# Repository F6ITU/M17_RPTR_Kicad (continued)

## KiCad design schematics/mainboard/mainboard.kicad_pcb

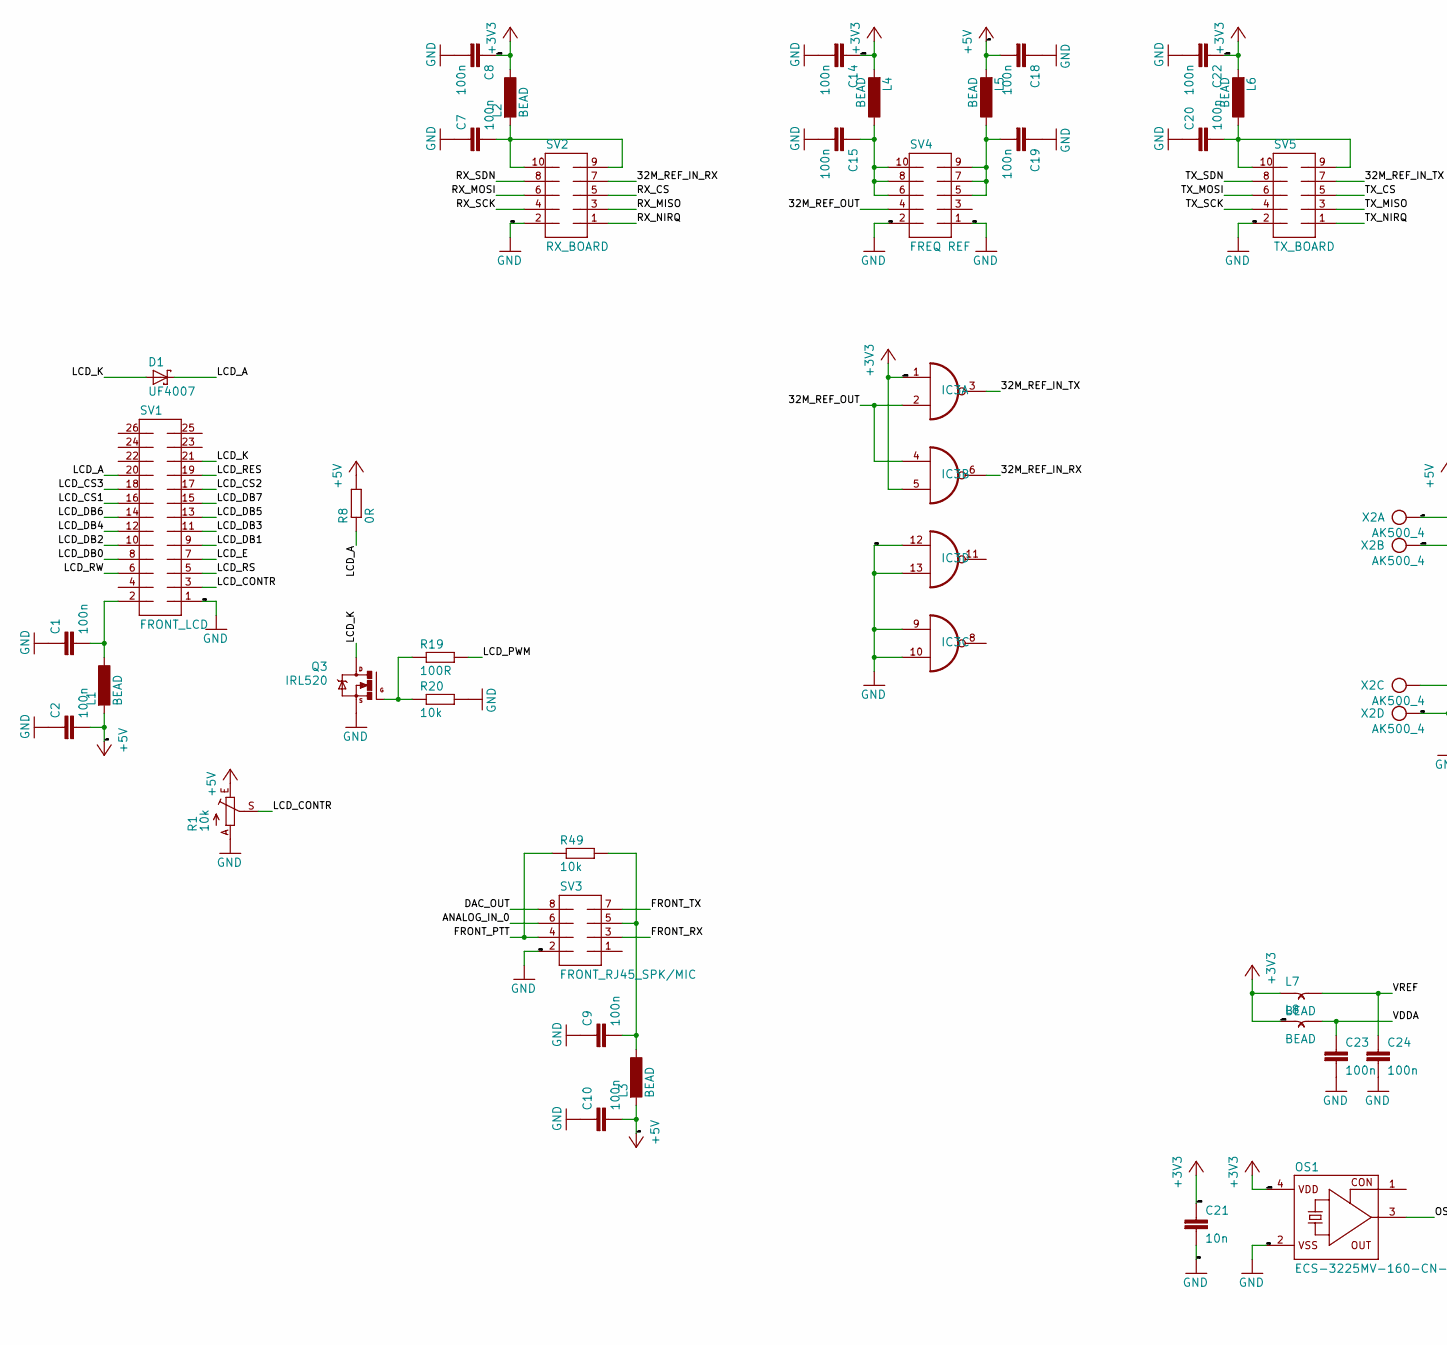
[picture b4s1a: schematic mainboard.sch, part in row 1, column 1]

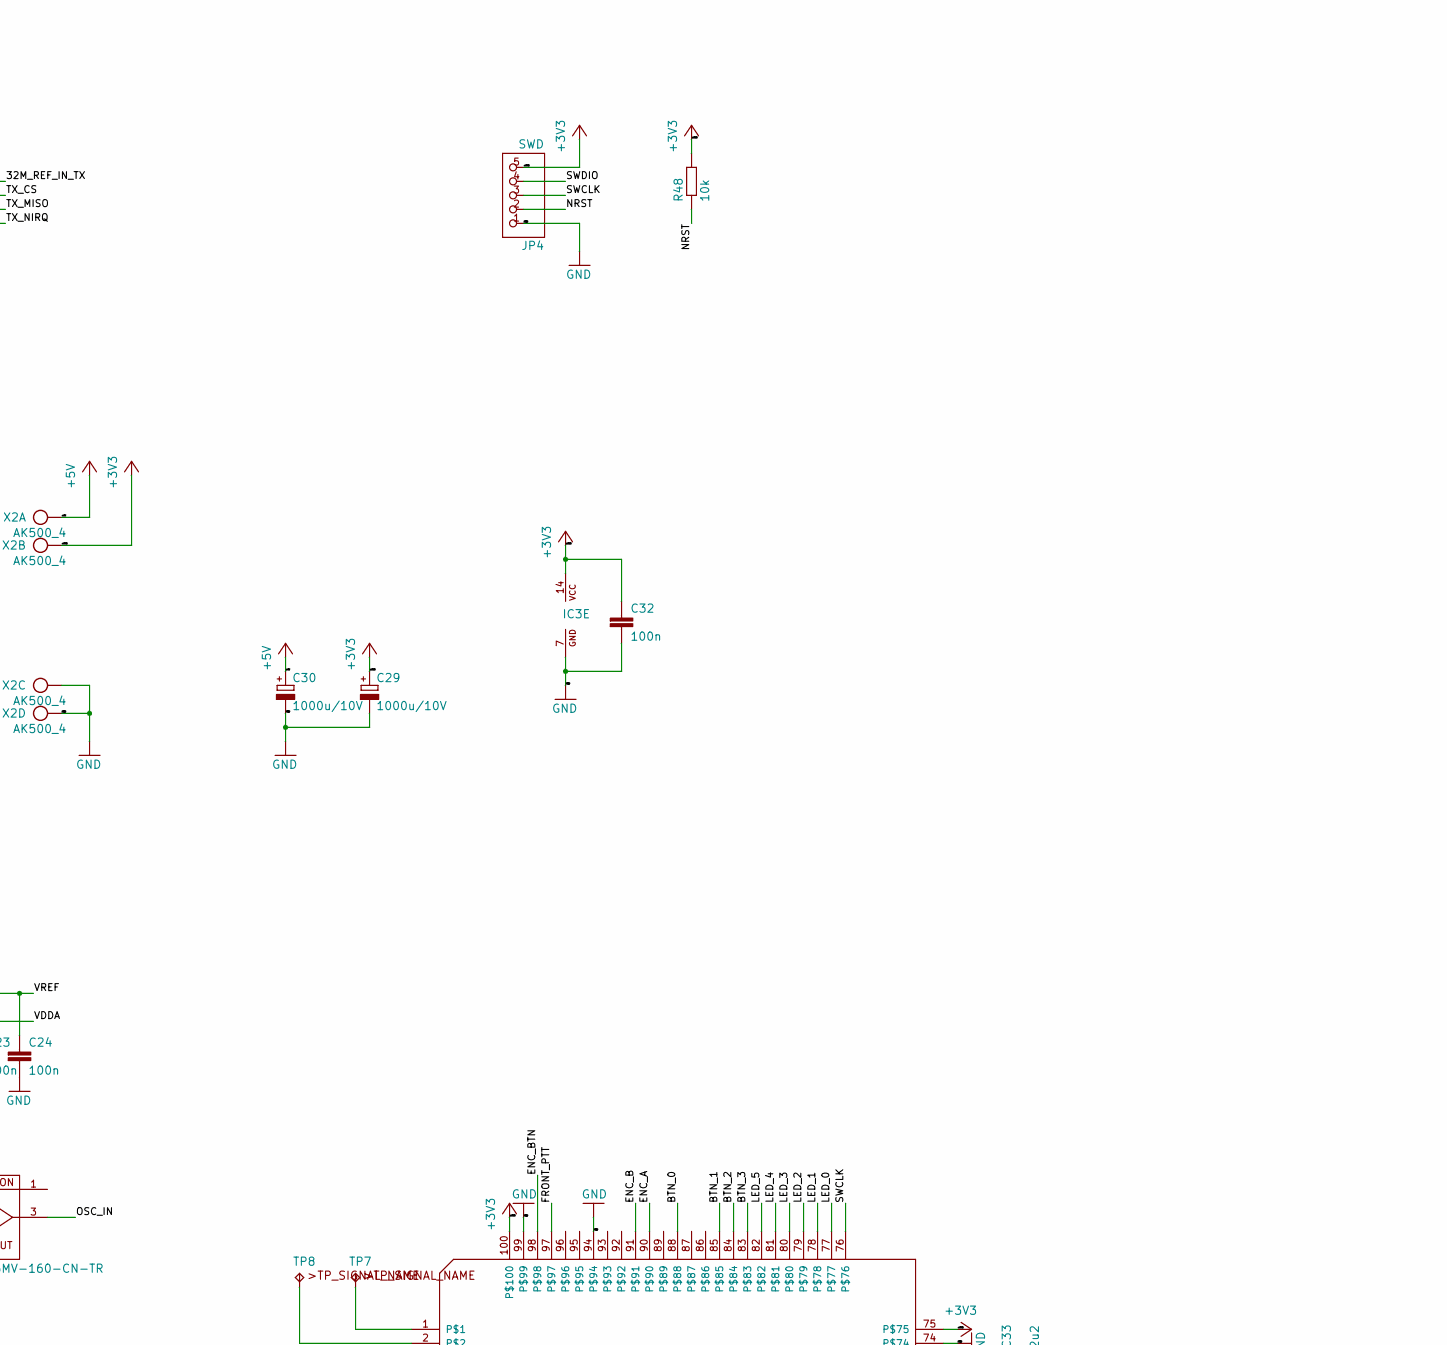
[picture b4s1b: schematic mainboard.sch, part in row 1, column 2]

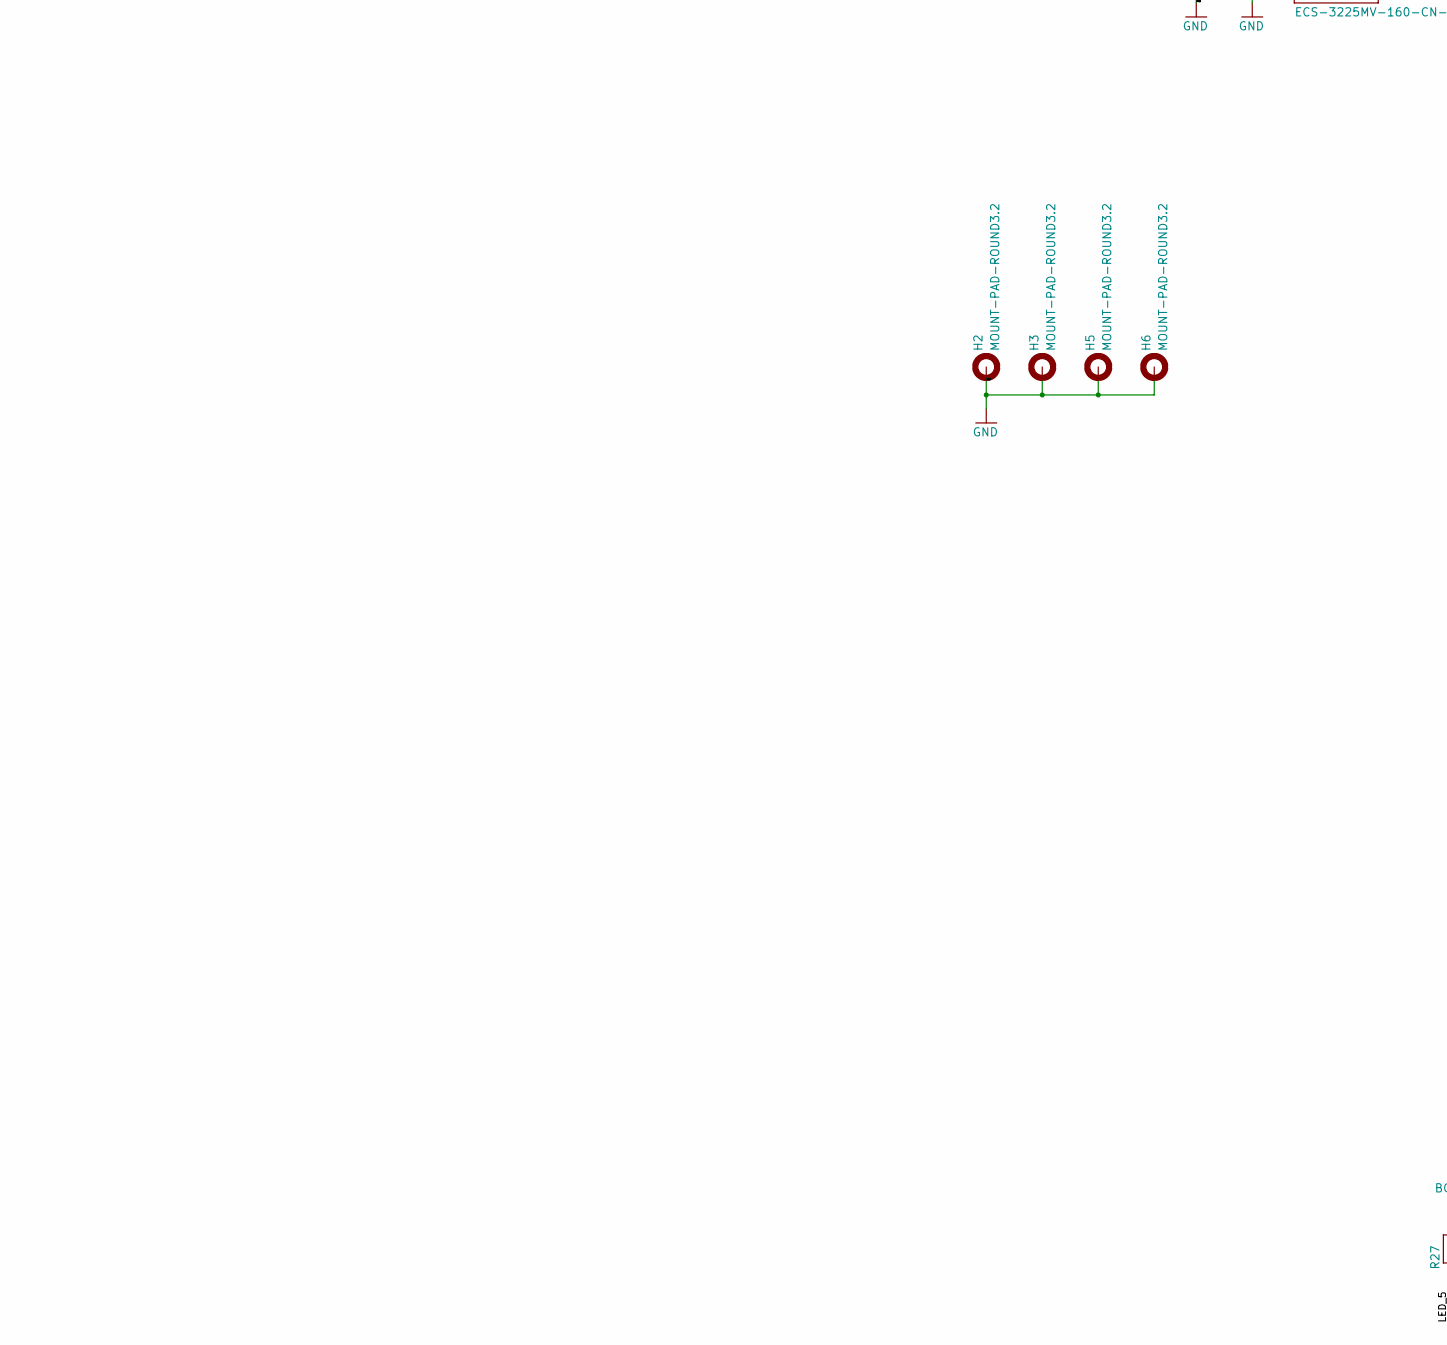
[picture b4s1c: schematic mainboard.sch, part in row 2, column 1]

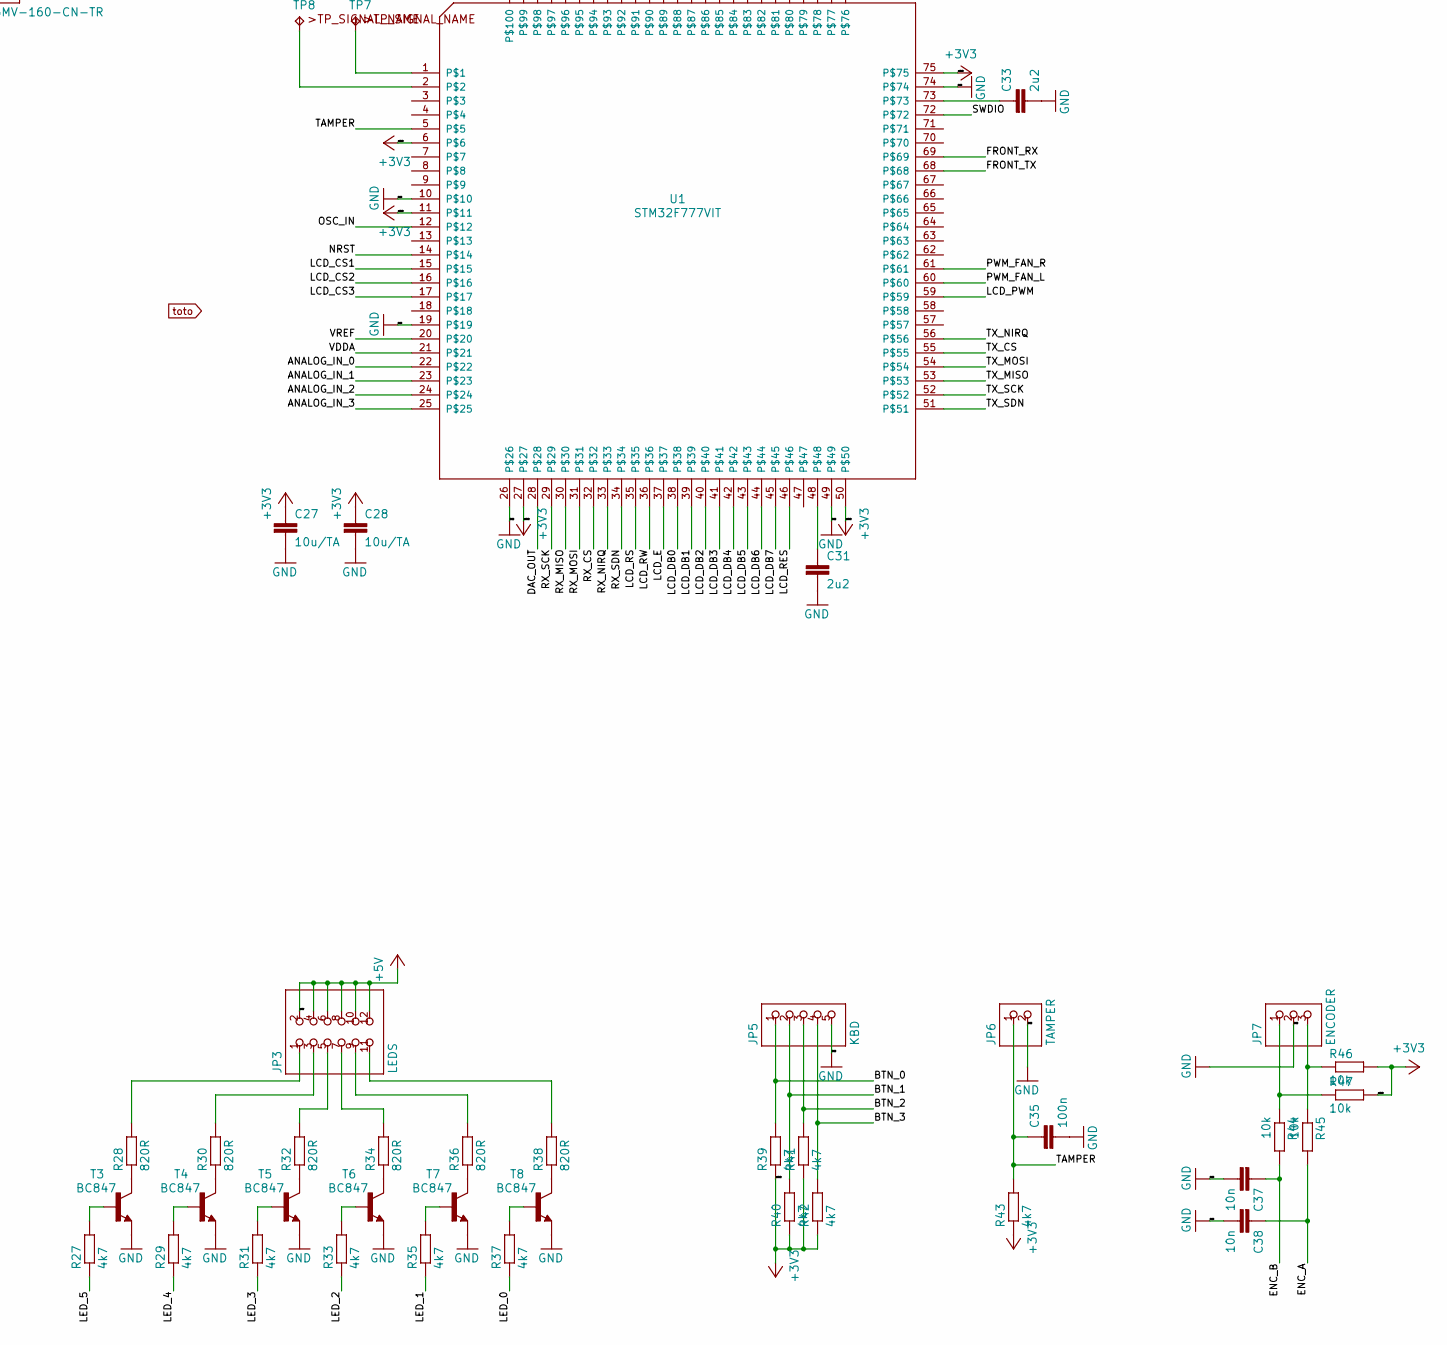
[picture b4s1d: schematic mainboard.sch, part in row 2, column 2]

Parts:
C1, C2, C7, C8, C9, C10, C14, C15, C18, C19, C20, C22, C23, C24, C32, C35: 100n; C0805
C21, C37, C38: 10n; C0805
C27, C28: 10u/TA; C1206
C29, C30: 1000u/10V; E3,5-8
C31, C33: 2u2; C0805
D1: UF4007; DO41-7.6
H2, H3, H5, H6: MOUNT-PAD-ROUND3.2; 3,2-PAD
IC3: 74AHC00D; SO14
JP3: LEDS; 2X06
JP4: SWD; 1X05
JP5: KBD; 1X05
JP6: TAMPER; 1X02
JP7: ENCODER; 1X03
L1, L2, L3, L4, L5, L6: BEAD; 0204_7
L7, L8: BEAD; SM-B5
OS1: ECS-3225MV-160-CN-TR; 3.4X2.7-4-PAD
Q3: IRL520; TO220BV
R1: 10k; CA6V
R8: 0R; R1206
R19: 100R; R0805
R20, R44, R45, R46, R47, R48, R49: 10k; R0805
R27, R29, R31, R33, R35, R37, R39, R40, R41, R42, R43: 4k7; R0805
R28, R30, R32, R34, R36, R38: 820R; R0805
SV1: FRONT_LCD; ML26
SV2: RX_BOARD; ML10
SV3: FRONT_RJ45_SPK/MIC; MA04-2
SV4: FREQ REF; ML10
SV5: TX_BOARD; ML10
T3, T4, T5, T6, T7, T8: BC847; SOT23
TP7, TP8: TPB2,54; B2,54
U1: STM32F777VIT; LQFP100
X2: AK500_4

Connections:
+3V3: C8.1, C14.1, C21.1, C22.1, C27.1, C28.1, C29.+, C32.1, IC3.1 (I0), IC3.5 (I1), IC3.14 (VCC), JP4.5, L2.1, L4.2, L6.2, L7.1, L8.1, OS1.4 (VDD), R39.1, R40.1, R41.1, R42.1, R43.1, R46.2, R47.2, R48.2, U1.6, U1.11, U1.27, U1.50, U1.75, U1.100, X2.2
+5V: C2.2, C10.2, C18.2, C30.+, JP3.2, JP3.4, JP3.6, JP3.8, JP3.10, JP3.12, L1.2, L3.2, L5.2, R1.E, R8.2, X2.1
/32M_REF_IN_RX: IC3.6 (O), SV2.7
/32M_REF_IN_TX: IC3.3 (O), SV5.7
/32M_REF_OUT: IC3.2 (I1), IC3.4 (I0), SV4.4
/ANALOG_IN_0: SV3.6, U1.22
/ANALOG_IN_1: U1.23
/ANALOG_IN_2: U1.24
/ANALOG_IN_3: U1.25
/BTN_0: JP5.1, R39.2, U1.88
/BTN_1: JP5.2, R40.2, U1.85
/BTN_2: JP5.3, R41.2, U1.84
/BTN_3: JP5.4, R42.2, U1.83
/DAC_OUT: SV3.8, U1.28
/ENC_A: C38.1, R45.2, U1.90
/ENC_B: C37.1, R44.2, U1.91
/ENC_BTN: U1.98
/FRONT_PTT: R49.1, SV3.4, U1.97
/FRONT_RX: SV3.3, U1.69
/FRONT_TX: SV3.7, U1.68
/LCD_A: D1.C, R8.1, SV1.20
/LCD_CONTR: R1.S, SV1.3
/LCD_CS1: SV1.16, U1.15
/LCD_CS2: SV1.17, U1.16
/LCD_CS3: SV1.18, U1.17
/LCD_DB0: SV1.8, U1.38
/LCD_DB1: SV1.9, U1.39
/LCD_DB2: SV1.10, U1.40
/LCD_DB3: SV1.11, U1.41
/LCD_DB4: SV1.12, U1.42
/LCD_DB5: SV1.13, U1.43
/LCD_DB6: SV1.14, U1.44
/LCD_DB7: SV1.15, U1.45
/LCD_E: SV1.7, U1.37
/LCD_K: D1.A, Q3.D, SV1.21
/LCD_PWM: R19.2, U1.59
/LCD_RES: SV1.19, U1.46
/LCD_RS: SV1.5, U1.35
/LCD_RW: SV1.6, U1.36
/LED_0: R37.1, U1.77
/LED_1: R35.1, U1.78
/LED_2: R33.1, U1.79
/LED_3: R31.1, U1.80
/LED_4: R29.1, U1.81
/LED_5: R27.1, U1.82
/NRST: JP4.2, R48.1, U1.14
/OSC_IN: OS1.3 (OUT), U1.12
/PWM_FAN_L: U1.60
/PWM_FAN_R: U1.61
/RX_CS: SV2.5, U1.32
/RX_MISO: SV2.3, U1.30
/RX_MOSI: SV2.6, U1.31
/RX_NIRQ: SV2.1, U1.33
/RX_SCK: SV2.4, U1.29
/RX_SDN: SV2.8, U1.34
/SWCLK: JP4.3, U1.76
/SWDIO: JP4.4, U1.72
/TAMPER: C35.1, JP6.1, R43.2, U1.5
/TX_CS: SV5.5, U1.55
/TX_MISO: SV5.3, U1.53
/TX_MOSI: SV5.6, U1.54
/TX_NIRQ: SV5.1, U1.56
/TX_SCK: SV5.4, U1.52
/TX_SDN: SV5.8, U1.51
/VDDA: C23.1, L8.2, U1.21
/VREF: C24.1, L7.2, U1.20
GND: C1.1, C2.1, C7.1, C8.2, C9.1, C10.1, C14.2, C15.2, C18.1, C19.1, C20.1, C21.2, C22.2, C23.2, C24.2, C27.2, C28.2, C29.-, C30.-, C31.2, C32.2, C33.2, C35.2, C37.2, C38.2, H2.B3,2, H3.B3,2, H5.B3,2, H6.B3,2, IC3.7 (GND), IC3.9 (I0), IC3.10 (I1), IC3.12 (I0), IC3.13 (I1), JP4.1, JP5.5, JP6.2, JP7.2, OS1.2 (VSS), Q3.S, R1.A, R20.2, SV1.1, SV2.2, SV3.2, SV4.1, SV4.2, SV5.2, T3.2 (E), T4.2 (E), T5.2 (E), T6.2 (E), T7.2 (E), T8.2 (E), U1.10, U1.19, U1.26, U1.49, U1.74, U1.94, U1.99, X2.3, X2.4
unnamed: C1.2, L1.1, SV1.2
unnamed: C7.2, L2.2, SV2.9, SV2.10
unnamed: C9.2, L3.1, R49.2, SV3.5
unnamed: C15.1, L4.1, SV4.6, SV4.8, SV4.10
unnamed: C19.2, L5.1, SV4.5, SV4.7, SV4.9
unnamed: C20.2, L6.1, SV5.9, SV5.10
unnamed: C31.1, U1.48
unnamed: C33.1, U1.73
unnamed: JP3.1, R28.2
unnamed: JP3.3, R30.2
unnamed: JP3.5, R32.2
unnamed: JP3.7, R34.2
unnamed: JP3.9, R36.2
unnamed: JP3.11, R38.2
unnamed: JP7.1, R44.1, R47.1
unnamed: JP7.3, R45.1, R46.1
unnamed: Q3.G, R19.1, R20.1
unnamed: R27.2, T3.1 (B)
unnamed: R28.1, T3.3 (C)
unnamed: R29.2, T4.1 (B)
unnamed: R30.1, T4.3 (C)
unnamed: R31.2, T5.1 (B)
unnamed: R32.1, T5.3 (C)
unnamed: R33.2, T6.1 (B)
unnamed: R34.1, T6.3 (C)
unnamed: R35.2, T7.1 (B)
unnamed: R36.1, T7.3 (C)
unnamed: R37.2, T8.1 (B)
unnamed: R38.1, T8.3 (C)
unnamed: TP7.TP, U1.1
unnamed: TP8.TP, U1.2

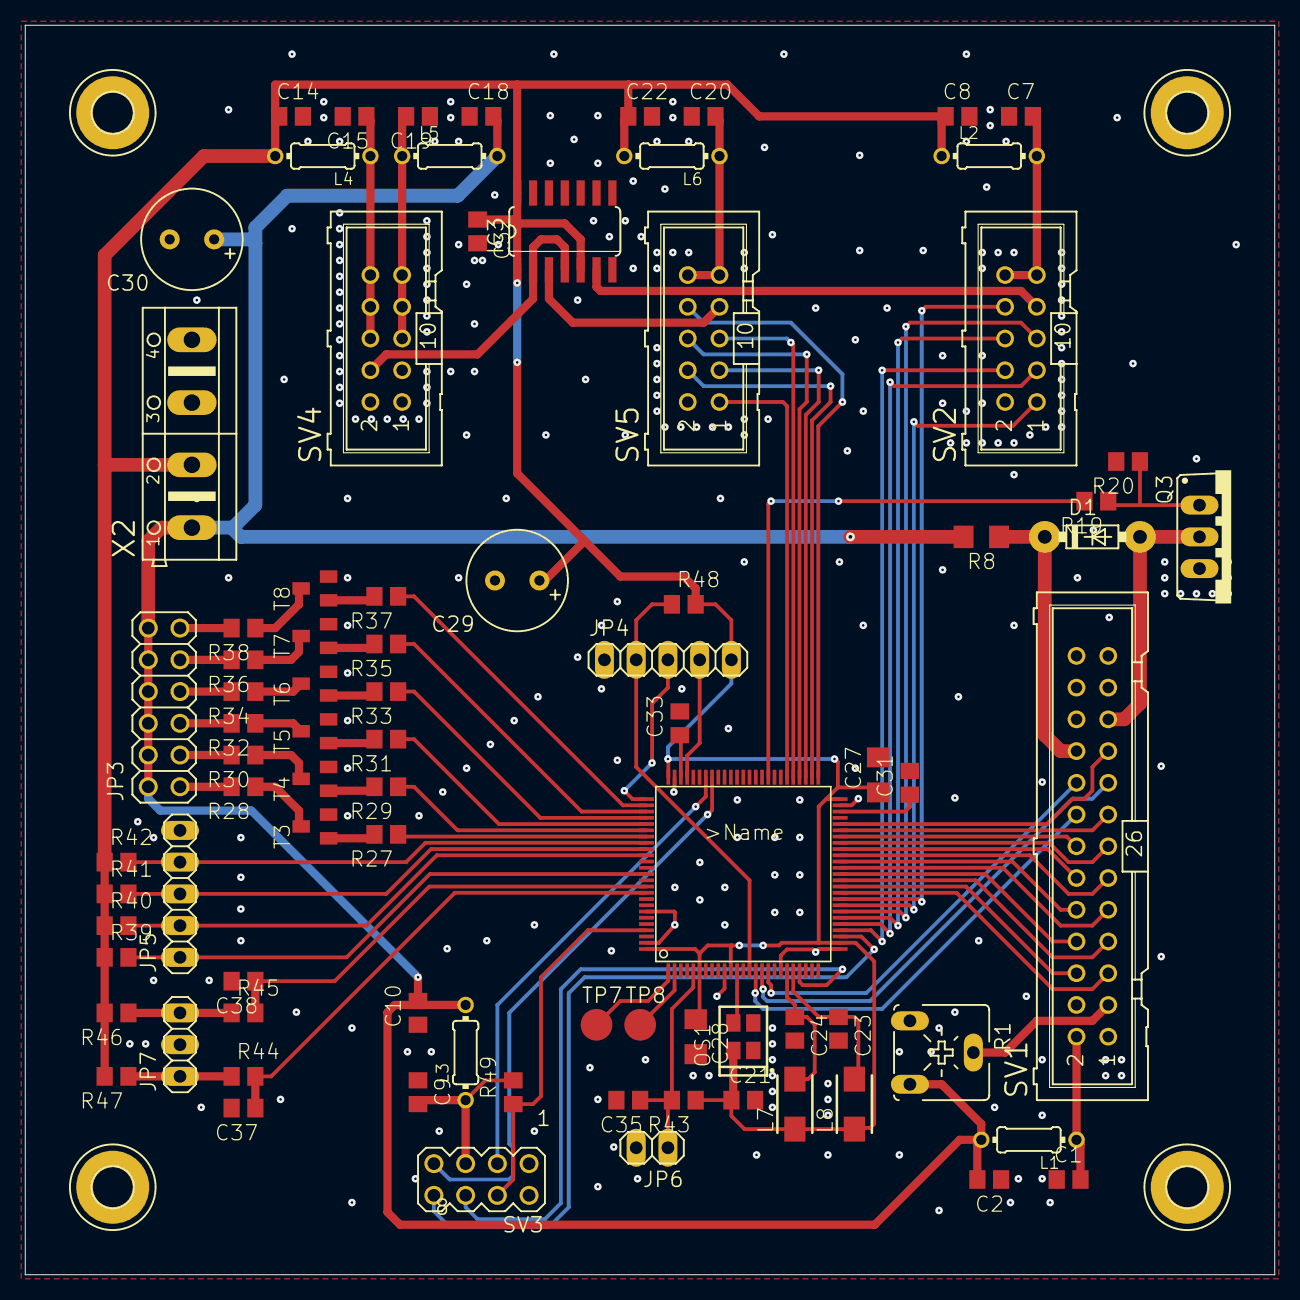
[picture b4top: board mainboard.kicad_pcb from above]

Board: 2 copper layers, 100.0 x 100.0 mm, 88 parts (0 on the bottom side), 92 nets.

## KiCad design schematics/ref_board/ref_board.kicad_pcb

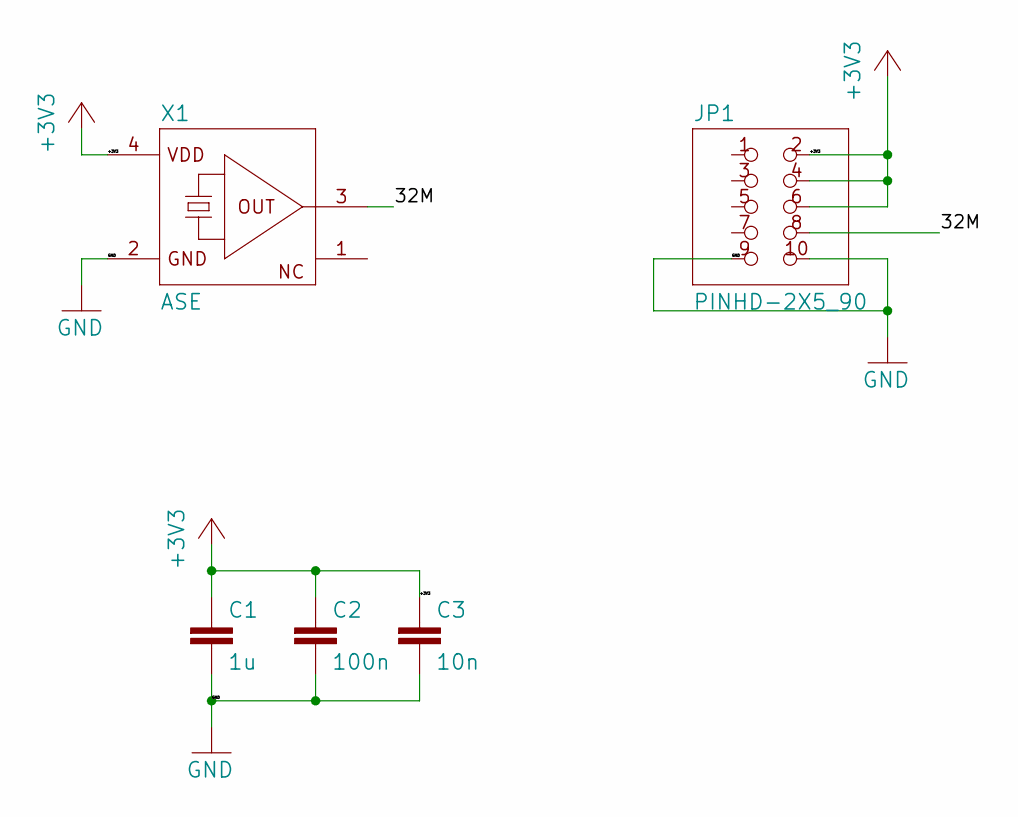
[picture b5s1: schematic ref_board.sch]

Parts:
C1: 1u; C1206
C2: 100n; C0805
C3: 10n; C0805
JP1: PINHD-2X5_90; 2X05_90
X1: ASE

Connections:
+3V3: C1.1, C2.1, C3.1, JP1.2, JP1.4, JP1.6, X1.4 (VDD)
/32M: JP1.8, X1.3 (OUT)
GND: C1.2, C2.2, C3.2, JP1.9, JP1.10, X1.2 (GND)

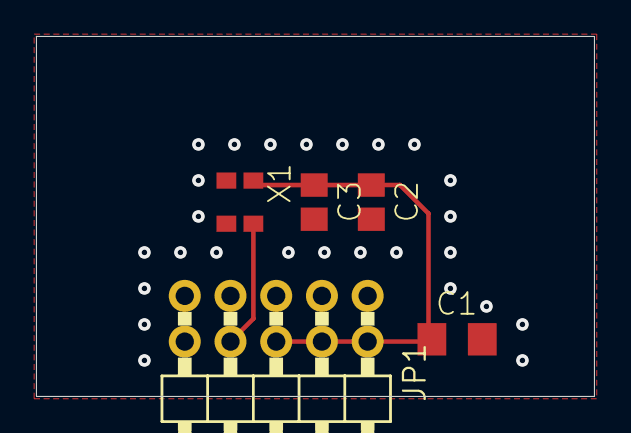
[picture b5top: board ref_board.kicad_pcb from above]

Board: 2 copper layers, 31.0 x 20.0 mm, 5 parts (0 on the bottom side), 3 nets.

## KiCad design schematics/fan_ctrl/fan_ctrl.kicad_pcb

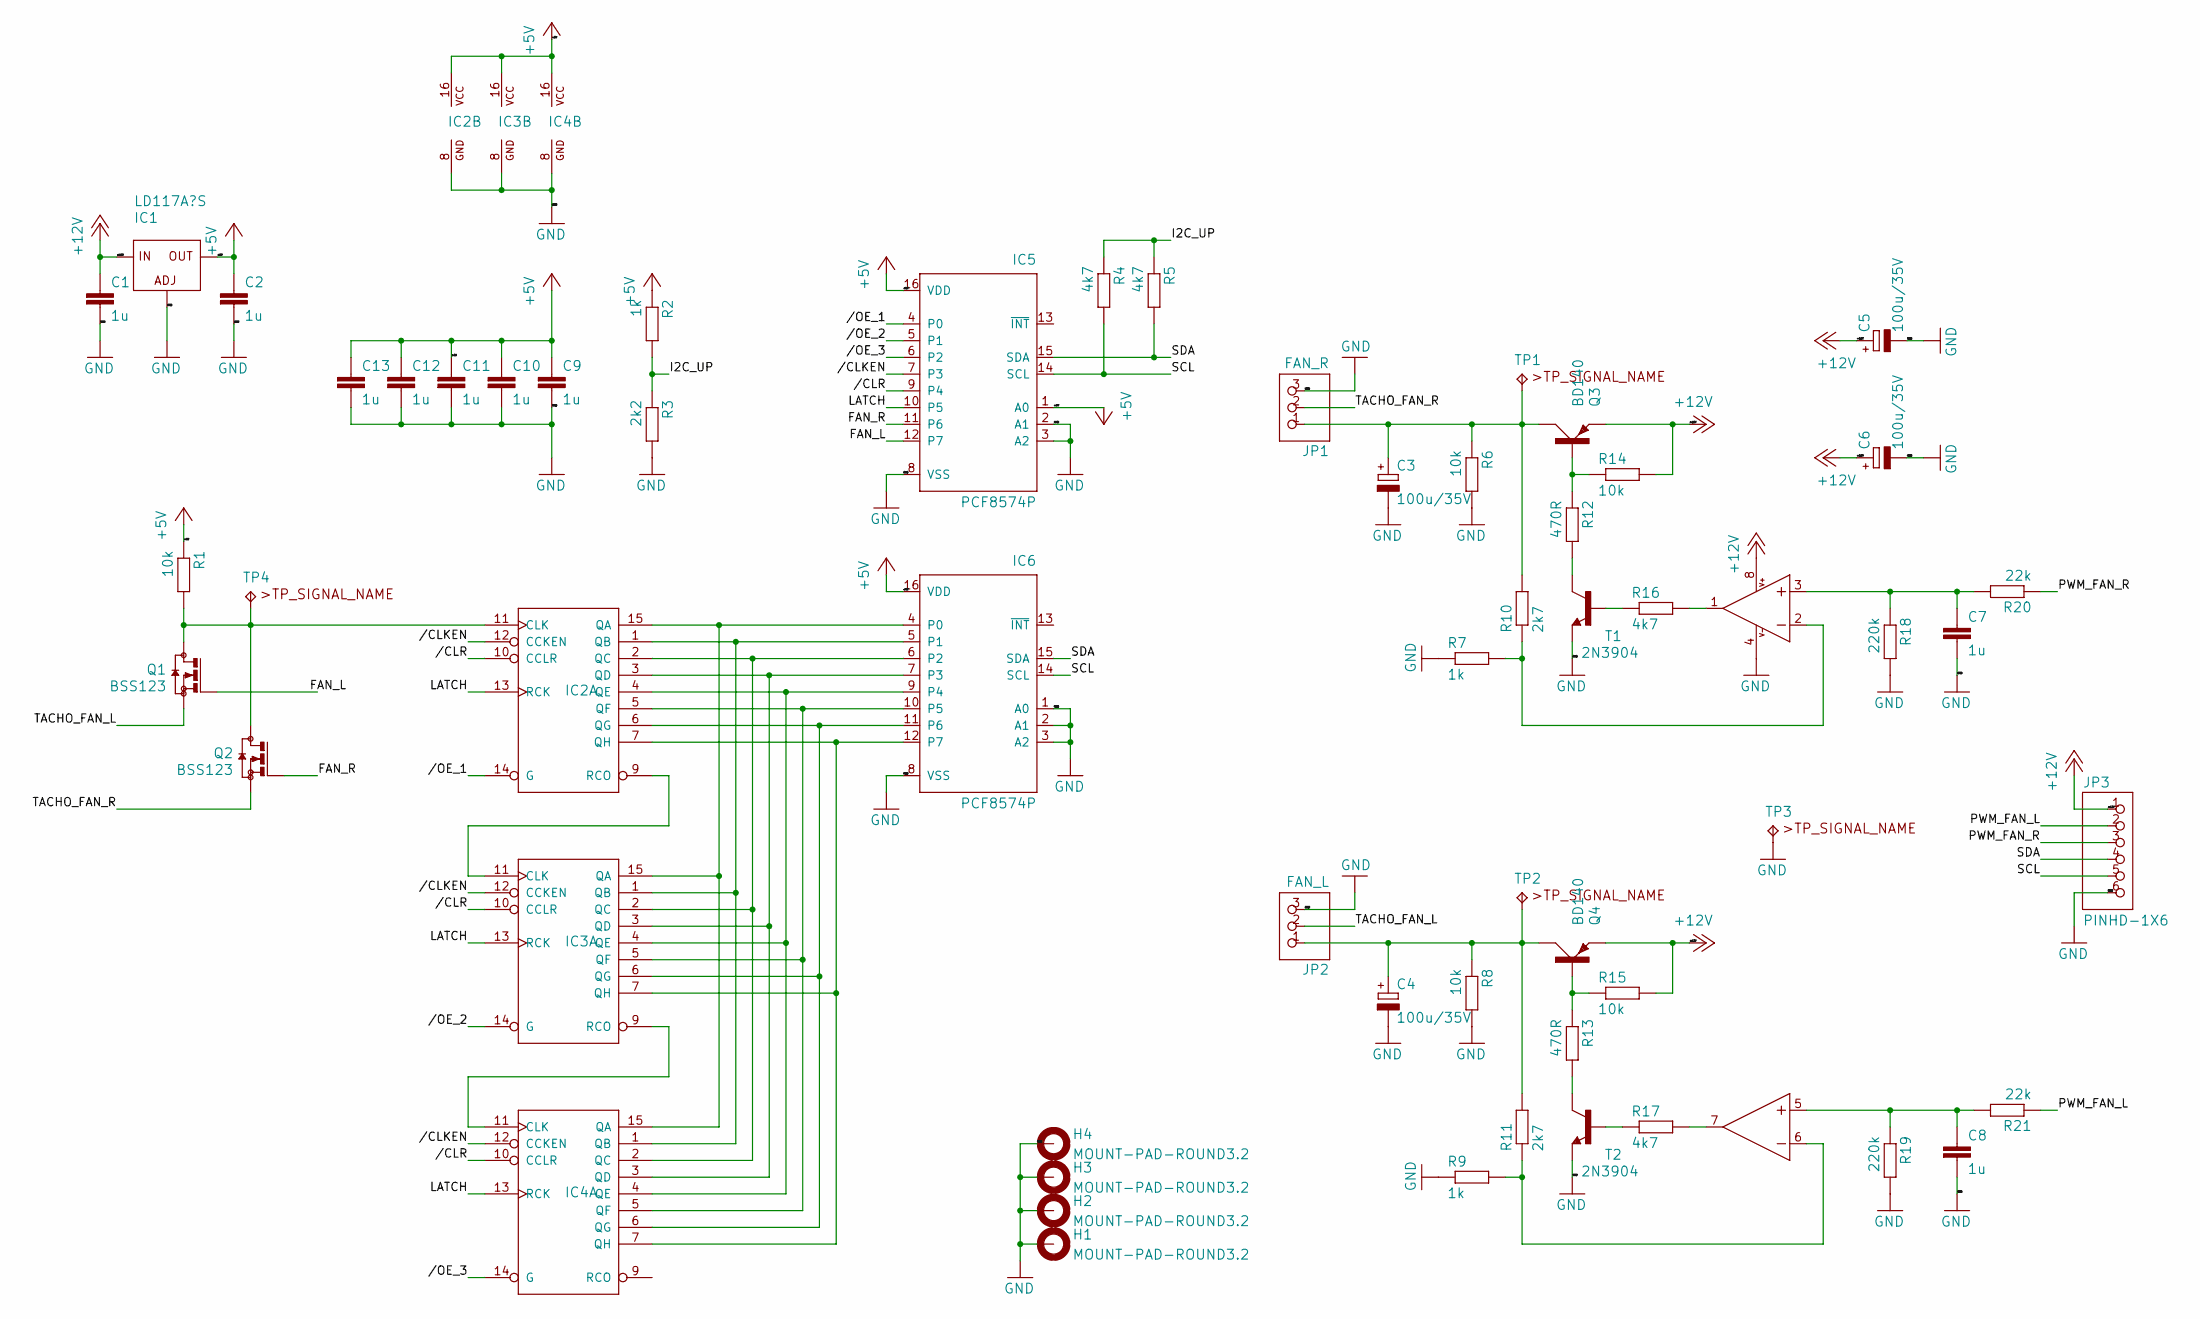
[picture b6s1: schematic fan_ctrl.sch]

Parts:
C1, C2, C7, C8, C9, C10, C11, C12, C13: 1u; C0805
C3, C4, C5, C6: 100u/35V; E3,5-8
H1, H2, H3, H4: MOUNT-PAD-ROUND3.2; 3,2-PAD
IC1: LD117A?S; SOT223
IC2, IC3, IC4: 74590N; DIL16
IC5, IC6: PCF8574P; DIL16
IC7: LM358N; DIL08
JP1: FAN_R; 1X03
JP2: FAN_L; 1X03
JP3: PINHD-1X6; 1X06
Q1, Q2: BSS123; SOT23
Q3, Q4: BD140; TO126AV
R1, R6, R8, R14, R15: 10k; R0805
R2, R7, R9: 1k; R0805
R3: 2k2; R0805
R4, R5, R16, R17: 4k7; R0805
R10, R11: 2k7; R0805
R12, R13: 470R; R0805
R18, R19: 220k; R0805
R20, R21: 22k; R0805
T1, T2: 2N3904; TO92-EBC
TP1, TP2, TP3, TP4: TPB2,54; B2,54

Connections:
+5V: C2.1, C9.1, C10.1, C11.1, C12.1, C13.1, IC1.4 (OUT), IC2.16 (VCC), IC3.16 (VCC), IC4.16 (VCC), IC5.1 (A0), IC5.16 (VDD), IC6.16 (VDD), R1.1, R2.1
+12V: C1.1, C5.+, C6.+, IC1.3 (IN), IC7.8 (V+), JP3.1, Q3.E, Q4.E, R14.2, R15.2
//CLKEN: IC2.12 (CCKEN), IC3.12 (CCKEN), IC4.12 (CCKEN), IC5.7 (P3)
//CLR: IC2.10 (CCLR), IC3.10 (CCLR), IC4.10 (CCLR), IC5.9 (P4)
//OE_1: IC2.14 (G), IC5.4 (P0)
//OE_2: IC3.14 (G), IC5.5 (P1)
//OE_3: IC4.14 (G), IC5.6 (P2)
/FAN_L: IC5.12 (P7), Q1.1 (G)
/FAN_R: IC5.11 (P6), Q2.1 (G)
/I2C_UP: R2.2, R3.1, R4.1, R5.1
/LATCH: IC2.13 (RCK), IC3.13 (RCK), IC4.13 (RCK), IC5.10 (P5)
/PWM_FAN_L: JP3.2, R21.1
/PWM_FAN_R: JP3.3, R20.1
/SCL: IC5.14 (SCL), IC6.14 (SCL), JP3.5, R4.2
/SDA: IC5.15 (SDA), IC6.15 (SDA), JP3.4, R5.2
/TACHO_FAN_L: JP2.2, Q1.2 (S)
/TACHO_FAN_R: JP1.2, Q2.2 (S)
GND: C1.2, C2.2, C3.-, C4.-, C5.-, C6.-, C7.2, C8.2, C9.2, C10.2, C11.2, C12.2, C13.2, H1.B3,2, H2.B3,2, H3.B3,2, H4.B3,2, IC1.1 (ADJ), IC2.8 (GND), IC3.8 (GND), IC4.8 (GND), IC5.2 (A1), IC5.3 (A2), IC5.8 (VSS), IC6.1 (A0), IC6.2 (A1), IC6.3 (A2), IC6.8 (VSS), IC7.4 (V-), JP1.3, JP2.3, JP3.6, R3.2, R6.2, R7.1, R8.2, R9.1, R18.2, R19.2, T1.E, T2.E, TP3.TP
unnamed: C3.+, JP1.1, Q3.C, R6.1, R10.2, TP1.TP
unnamed: C4.+, JP2.1, Q4.C, R8.1, R11.2, TP2.TP
unnamed: C7.1, IC7.3 (+IN), R18.1, R20.2
unnamed: C8.1, IC7.5 (+IN), R19.1, R21.2
unnamed: IC2.1 (QB), IC3.1 (QB), IC4.1 (QB), IC6.5 (P1)
unnamed: IC2.2 (QC), IC3.2 (QC), IC4.2 (QC), IC6.6 (P2)
unnamed: IC2.3 (QD), IC3.3 (QD), IC4.3 (QD), IC6.7 (P3)
unnamed: IC2.4 (QE), IC3.4 (QE), IC4.4 (QE), IC6.9 (P4)
unnamed: IC2.5 (QF), IC3.5 (QF), IC4.5 (QF), IC6.10 (P5)
unnamed: IC2.6 (QG), IC3.6 (QG), IC4.6 (QG), IC6.11 (P6)
unnamed: IC2.7 (QH), IC3.7 (QH), IC4.7 (QH), IC6.12 (P7)
unnamed: IC2.9 (RCO), IC3.11 (CLK)
unnamed: IC2.11 (CLK), Q1.3 (D), Q2.3 (D), R1.2, TP4.TP
unnamed: IC2.15 (QA), IC3.15 (QA), IC4.15 (QA), IC6.4 (P0)
unnamed: IC3.9 (RCO), IC4.11 (CLK)
unnamed: IC7.1 (OUT), R16.2
unnamed: IC7.2 (-IN), R7.2, R10.1
unnamed: IC7.6 (-IN), R9.2, R11.1
unnamed: IC7.7 (OUT), R17.2
unnamed: Q3.B, R12.1, R14.1
unnamed: Q4.B, R13.1, R15.1
unnamed: R12.2, T1.C
unnamed: R13.2, T2.C
unnamed: R16.1, T1.B
unnamed: R17.1, T2.B

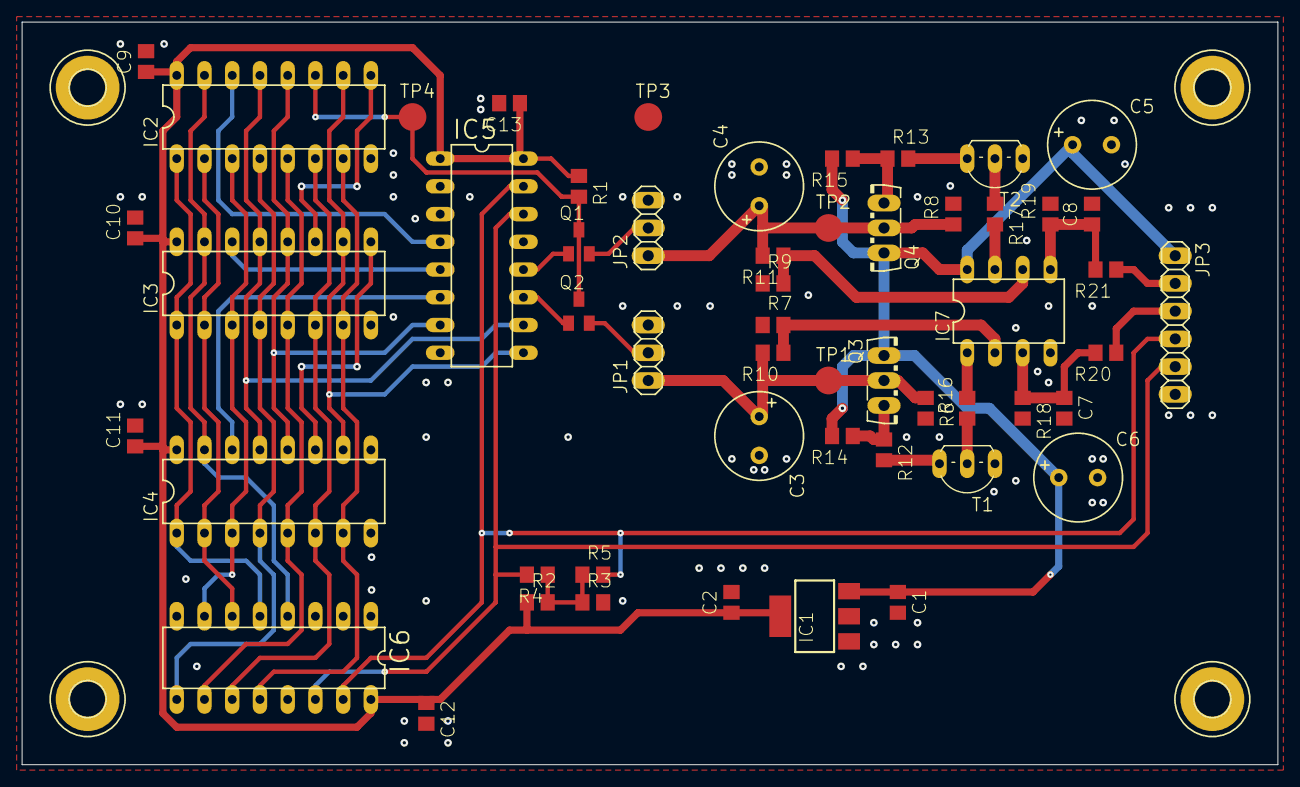
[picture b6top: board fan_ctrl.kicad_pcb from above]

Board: 2 copper layers, 115.0 x 68.0 mm, 58 parts (0 on the bottom side), 43 nets.

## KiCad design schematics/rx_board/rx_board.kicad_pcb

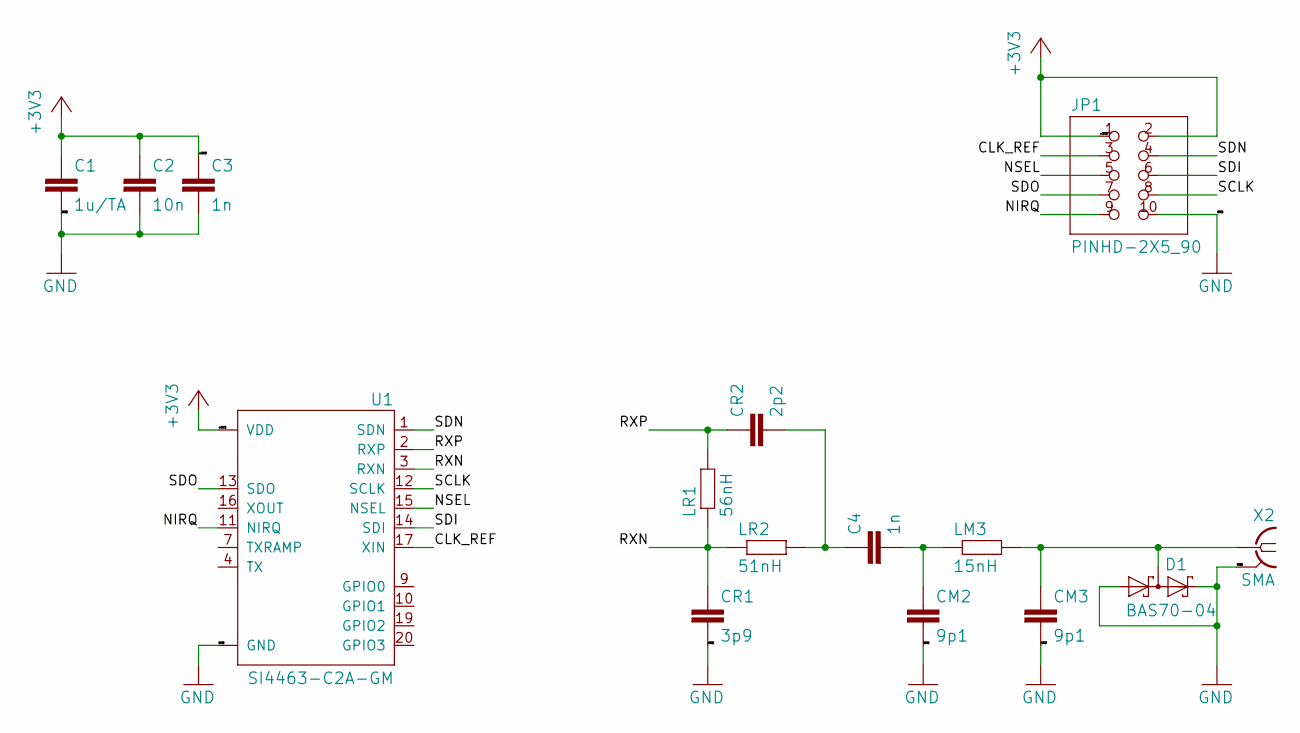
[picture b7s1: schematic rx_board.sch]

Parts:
C1: 1u/TA; C1206
C2: 10n; C0805
C3, C4: 1n; C0805
CM2, CM3: 9p1; C0805
CR1: 3p9; C0805
CR2: 2p2; C0805
D1: BAS70-04; SOT23
JP1: PINHD-2X5_90; 2X05_90
LM3: 15nH; R0805
LR1: 56nH; R0805
LR2: 51nH; R0805
U1: SI4463-C2A-GM; QFN50P400X400X90-20N
X2: SMA; J502-ND-142-0701-871_876

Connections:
+3V3: C1.1, C2.1, C3.1, JP1.1, JP1.2, U1.6 (VDD), U1.8 (VDD)
/CLK_REF: JP1.3, U1.17 (XIN)
/NIRQ: JP1.9, U1.11 (NIRQ)
/NSEL: JP1.5, U1.15 (NSEL)
/RXN: CR1.1, LR1.1, LR2.1, U1.3 (RXN)
/RXP: CR2.1, LR1.2, U1.2 (RXP)
/SCLK: JP1.8, U1.12 (SCLK)
/SDI: JP1.6, U1.14 (SDI)
/SDN: JP1.4, U1.1 (SDN)
/SDO: JP1.7, U1.13 (SDO)
GND: C1.2, C2.2, C3.2, CM2.2, CM3.2, CR1.2, D1.1 (A1), D1.2 (C2), JP1.10, U1.18 (GND), U1.21 (GND), X2.G@1 (2), X2.G@2 (2), X2.G@3 (2), X2.G@4 (2)
unnamed: C4.1, CR2.2, LR2.2
unnamed: C4.2, CM2.1, LM3.1
unnamed: CM3.1, D1.3 (C1A2), LM3.2, X2.1

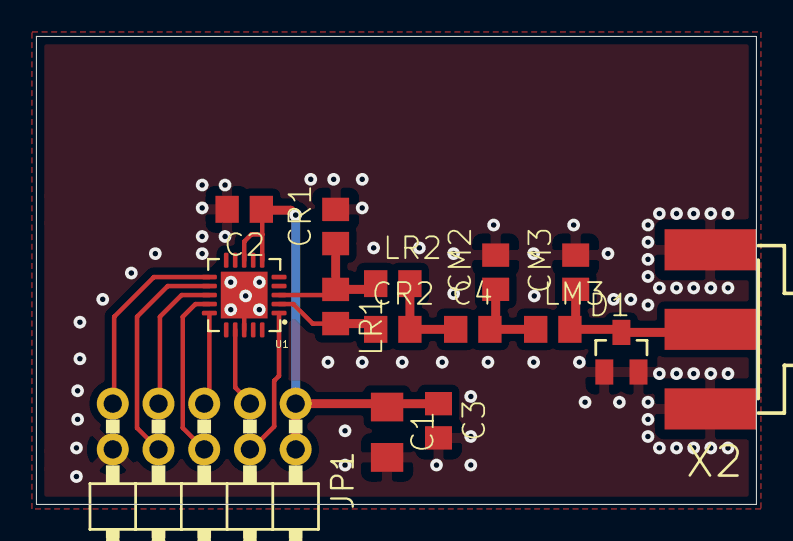
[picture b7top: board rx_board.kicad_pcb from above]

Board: 2 copper layers, 40.0 x 26.0 mm, 15 parts (0 on the bottom side), 14 nets.

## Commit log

2020-09-07 raw KiCADtranslation of the original M17Repeater (1st commit)
2020-09-10 first complete design & routing
2020-09-10 some cleaning
2020-09-10 Silk mask cleaning, better decoupling
2020-09-14 shielded version
2020-09-14 common lib added
2020-09-14 datasheet folder added
2020-09-15 PA boad smd version, 50Ohms microstrip
